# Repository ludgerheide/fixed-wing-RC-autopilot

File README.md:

# Autopilot for a fixed-wing, three-axis RC plane

This code should become an autopilot (waypoint-following or fly-by-wire with gust compensation) for an RC plane someday.

##Hardware used

* ATMEGA2560 microcontroller
* NMEA GPS (Adafruit ultimate GPS used)
* L3GD20 Gyro (Adafruit 10DOF imu board used)
* LSM303DLHC Magnetomenter/Accelerometer (also on adafruit 10dof)
* BMP180 barometer/altimeter (also on the 10DOF board)
* xBee-API compatible transceiver (xBee PRO 868 used)

## Software requirements

* avr-gcc and avr-libc
* Google's protobuf (version 2.6.1 used)
* nanopb

## Acknowledgements

This project contains code from the following sources:
* [The FreeIMU project](http://www.varesano.net/projects/hardware/FreeIMU)
* Madgwick's AHRS algorithm
* [Procyon AVRlib](http://www.procyonengineering.com/embedded/avr/avrlib/)
* Adafruit's various Arduino libraries for the 10DOF board

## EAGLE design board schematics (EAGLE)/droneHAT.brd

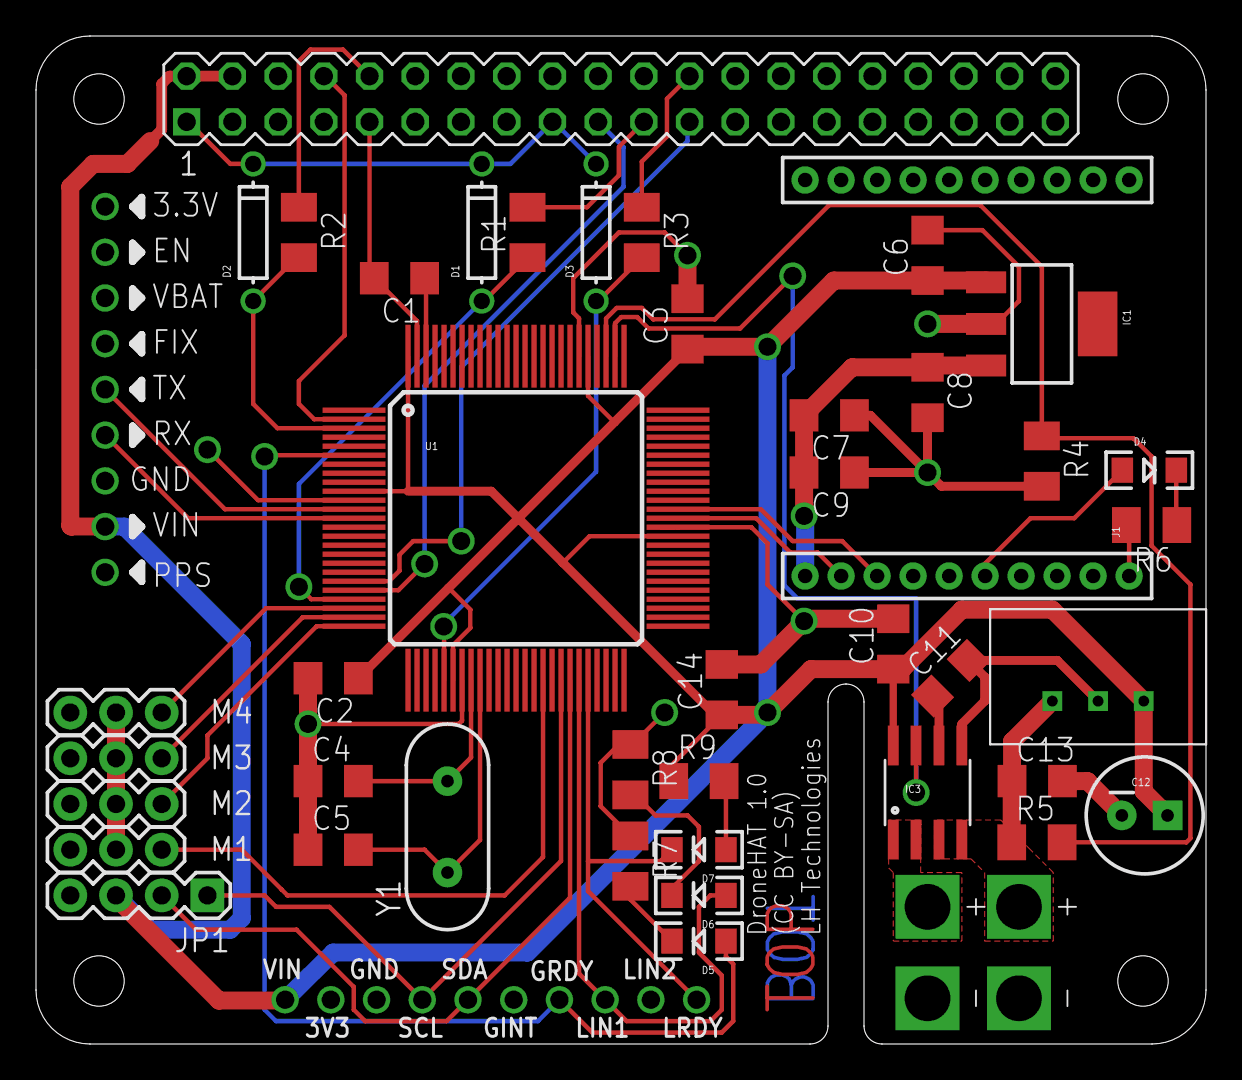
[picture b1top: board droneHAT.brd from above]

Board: 2 copper layers, 65.0 x 56.0 mm, 46 parts (0 on the bottom side), 40 nets.

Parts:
C1, C2, C3, C6, C7, C10, C14: 100n; C1206
C4, C5: 22p; C1206
C8: 10u; C1206
C9: 68p; C1206
C11: 1n; C1206
C12: 330u; CPOL-RADIAL-100UF-25V
C13: 100n/HV; C1206
D1, D2, D3: DO-1N4148
D4, D5, D6, D7: GREEN; LED-1206
IC1: V_REG_MIC2920; SOT223
IC2: 5V; TSRN1
IC3: ACS712; SO08
J1: XBEE-1B1; XBEE-1
J2, J5: BAT; BAT_HDR
J3: ADAFRUITIMU; ADAIMU
J4: ADAFRUITGPS; ADAGPS
JP1: 1X04
K1: PIN20X2; PIN_20X2
M1, M2, M3, M4: SMALL_SERVO; 1X03
R1, R2, R3, R6, R7, R8, R9: 1k; M1206
R4: 1.5k; M1206
R5: 10k; M1206
U1: ATMEGA2560; TQFP100-LONG
Y1: 16MHz; HC49US

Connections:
3V3-INTERN: C7.2, C8.1, C9.2, IC1.3, J1.1
+3V3: D1.C, D2.C, D3.C, K1.1, K1.17
+5V: C2.1, C3.1, C6.1, C10.1, C12.1, C14.1, IC1.1, IC2.3, IC3.8, J3.VIN, J4.VIN, JP1.3, K1.2, K1.4, R9.1, U1.10, U1.31, U1.61, U1.80, U1.100
AVR-MISO: D1.A, R1.1, U1.22
AVR-MOSI: K1.19, U1.21
AVR-RST: D3.A, R3.2, U1.30
BAT_IN: IC3.1, IC3.2, J2.V+
GND: C1.2, C2.2, C3.2, C4.1, C5.1, C6.2, C7.1, C8.2, C9.1, C10.2, C11.2, C12.2, C13.2, C14.2, IC1.2, IC2.2, IC3.5, J1.10, J2.V-, J3.GND, J4.GND, J5.V-, JP1.4, K1.6, K1.9, K1.14, K1.20, K1.25, K1.30, K1.34, K1.39, M1.3, M2.3, M3.3, M4.3, R4.2, R6.2, R7.1, R8.1, U1.11, U1.32, U1.62, U1.81, U1.99
GRDY: D5.A, J3.GRDY, U1.6
LIN1: D6.A, J3.LIN1, U1.45
LRDY: D7.C, J3.LRDY, U1.46
unnamed: C1.1, U1.98
unnamed: M1.2, M2.2, M3.2, M4.2
unnamed: C11.1, IC3.6
unnamed: D4.A, J1.6
unnamed: D4.C, R6.1
unnamed: D5.C, R7.2
unnamed: K1.21, R1.2
unnamed: K1.24, R3.1
unnamed: K1.10, R2.1
unnamed: D6.C, R8.2
unnamed: D7.A, R9.2
unnamed: R4.1, R5.2, U1.78
unnamed: IC3.7, U1.77
RPI-RXD0: D2.A, R2.2, U1.3
RPI-TXD0: K1.8, U1.2
RX2: J4.TX, U1.12
RXD3: J1.2, U1.63
SCK: K1.23, U1.20
SCL: J3.SCL, JP1.1, U1.43
SDA: J3.SDA, JP1.2, U1.44
SERV1: M1.1, U1.41
SERV2: M2.1, U1.25
SERV3: M3.1, U1.24
SERV4: M4.1, U1.23
TX2: J4.RX, U1.13
TXD3: J1.3, U1.64
VIN: C13.1, IC2.1, IC3.3, IC3.4, J5.V+, R5.1
XTAL1: C5.2, U1.34, Y1.1
XTAL2: C4.2, U1.33, Y1.2

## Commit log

2015-10-05 moved more files into the repo
2015-10-05 updated gitignore
2015-10-05 Why?
2015-10-05 protobuf working
2015-10-07 One-way comms prototype
2015-10-07 Added Artificial Horizon (by dave47 from diydrones.com)
2015-10-09 Updated logging
2015-10-09 Added logging over UART
2015-10-09 Small fix
2015-10-09 Telemetry working now
2015-10-11 Servos + Telemetry
2015-10-12 Removed binary files
2015-10-12 Updated java project
2015-10-12 Updated Board
2015-10-16 Split View working
2015-10-17 Artificial horizon
2015-10-18 Added Serial Port
2015-10-19 Artificial Horizon + comms
2015-10-19 Made delegate weak
2015-10-24 Pin chan ges for production board
2015-10-24 Human-readable start seq
2015-10-24 Fuck STTY! the cause of the short messages was stay eating special chars :(
2015-10-25 Several updates
2015-10-25 Changed GPS
2015-10-25 Fixed a nasty GPS bug
2015-10-25 Accelerated horizon
2015-10-25 Better map view
2015-10-25 Removed autogenerated filed
2015-10-29 Added Xbox 360 controller support
2015-10-29 Fixed a nasty bug by a forgotten "volatile"
2015-10-29 Bidirectional comms and control
2015-11-04 Added controller output to PFD
2015-11-06 Added java Telemtry receiver (serial and udp networking)
2015-11-06 Updated java receiver/writer
2015-11-07 Java parser works now
2015-11-07 Update protobuf in AVR
2015-11-08 Added battery
2015-11-08 Battery with low-pass filter (1.5s rise time) + telemetry receiver with live graphing
2015-11-13 Added Flight Control Code
2015-11-15 Removed unnecessary logging
2015-11-15 Removed unnecessary logging, added battery
2015-11-15 Removed Warnings
2015-11-15 Added simple fly by wire
2015-11-15 Fixed memory leak
2015-11-15 Added sea level pressure update & save
2015-11-20 Dummy video
2015-12-09 Stuff
2015-12-09 Increased sensor update rate and timing precision
2015-12-10 Changes for -Wextra compilation
2015-12-10 Added fast inverse square root
2015-12-10 Added more fast functions for minor gains
2015-12-10 Better GPS and altitude
2015-12-13 Added compass calibration
2015-12-15 First trial of the new pitch controller
2015-12-15 PID Works now. Still needs calibration
2015-12-17 Bugfixes
2015-12-17 Initial yaw/course controller
2016-01-13 Added compass dump for calibration
2016-01-13 Added iOS Base code
2016-01-13 Allowed some autogenerated files
2016-01-14 Added basic components
2016-01-16 Added Logos
2016-01-18 Small changes to buiuld script and gitignore
2016-01-18 Removed TelemetryViewer
2016-01-18 Added new Java Comms Project
2016-01-20 installed pircbotx
2016-01-27 Added signed comms
2016-01-28 Updated to use the custom TCP relay, not IRC
2016-01-29 Chances to intellij
2016-01-29 Java/TCP working now
2016-01-29 Added file writer
2016-01-30 Minor updates to build environment
2016-02-02 Receiving in iOS
2016-02-03 Polyline WIP
2016-02-04 Track snapshot
2016-02-04 Updated some xCode files
2016-02-05 Changed to loggign class
2016-02-14 Waypoint completed
2016-02-17 Routes in testing
2016-02-20 Waypoints and route working
    Upload and delete/add not yet there
2016-02-20 added missing wayypoint options
2016-03-08 Grundgerüst flugregler
2016-03-08 Implemented altitude cascade
2016-03-09 Rate of turn controller
2016-03-09 Updated controller model
2016-03-09 Updated autopilot for new flight controler
2016-03-09 Failable Route Uplaod!
2016-03-09 Java bugfixes
2016-03-09 Route Uploading
2016-03-09 Added symlinks
2016-03-19 Added route to heading conversion
2016-03-22 Navigation Working
2016-04-07 Updated for git 2.2
2016-04-07 Updated to correspond to latest protobuf
2016-04-07 real values (as opposed to mock values for testing)
2016-04-07 Revert of f9d4eb049c527ec0a7191ddbd0a19be66f7ffb95
2016-04-08 Minor Bugfixes
2016-04-08 Deleted old flight controller code
2016-04-08 Dleted Simulink
2016-04-08 Implemented Autonomous
    TODO:
    –autopilot receives msgs over serial
    –autopilot saves homeBase to EEPROM and loads on boot
2016-04-10 Various bugfixes, UDP broadcast
2016-04-10 Updated altitude controller
2016-04-10 Comms with RasPi over Serial
2016-04-10 512 bit is enough, minor bugfix
2016-04-14 Misc Fixes
    flown 2016-04-13
2016-04-14 Added pi IP for hotspot
2016-04-14 Misc Bugfixes
2016-04-14 Deleted Flugregler on windows
2016-04-14 Deleted output files fdrom repo
2016-04-19 Added autonomous update
    hard-to use dev version
2016-04-19 Removed whitespace
2016-04-21 Fixed plane turning wrong way
2016-04-21 Minor perf improvement
2016-05-02 Added evaluation scipts
2016-05-02 New makefile for magDump
2016-05-02 Updated pitch/altitude controller
2016-05-02 Better default altitude
2016-05-03 Moved evaluation files
2016-05-30 Updated Analysis scripts
2016-05-30 Reduced pitch angle variance
2016-05-30 Changes to autonomous mode
2017-08-15 Made GPS way faster
2017-08-15 Updated xcode Project
2017-08-15 Changes to configuration found by testing
2017-08-15 Updated paths in script
2017-08-15 Updated Makefile
2017-08-15 Updated nanopb
2017-08-17 Updated Protobuf and swift-3

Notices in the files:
board schematics (EAGLE)/droneHAT.brd:
(CC BY-SA)
parts and their libraries:
SparkFun-DigitalIC: Licensing: Creative Commons ShareAlike 4.0 International - https://creativecommons.org/licenses/by-sa/4.0
